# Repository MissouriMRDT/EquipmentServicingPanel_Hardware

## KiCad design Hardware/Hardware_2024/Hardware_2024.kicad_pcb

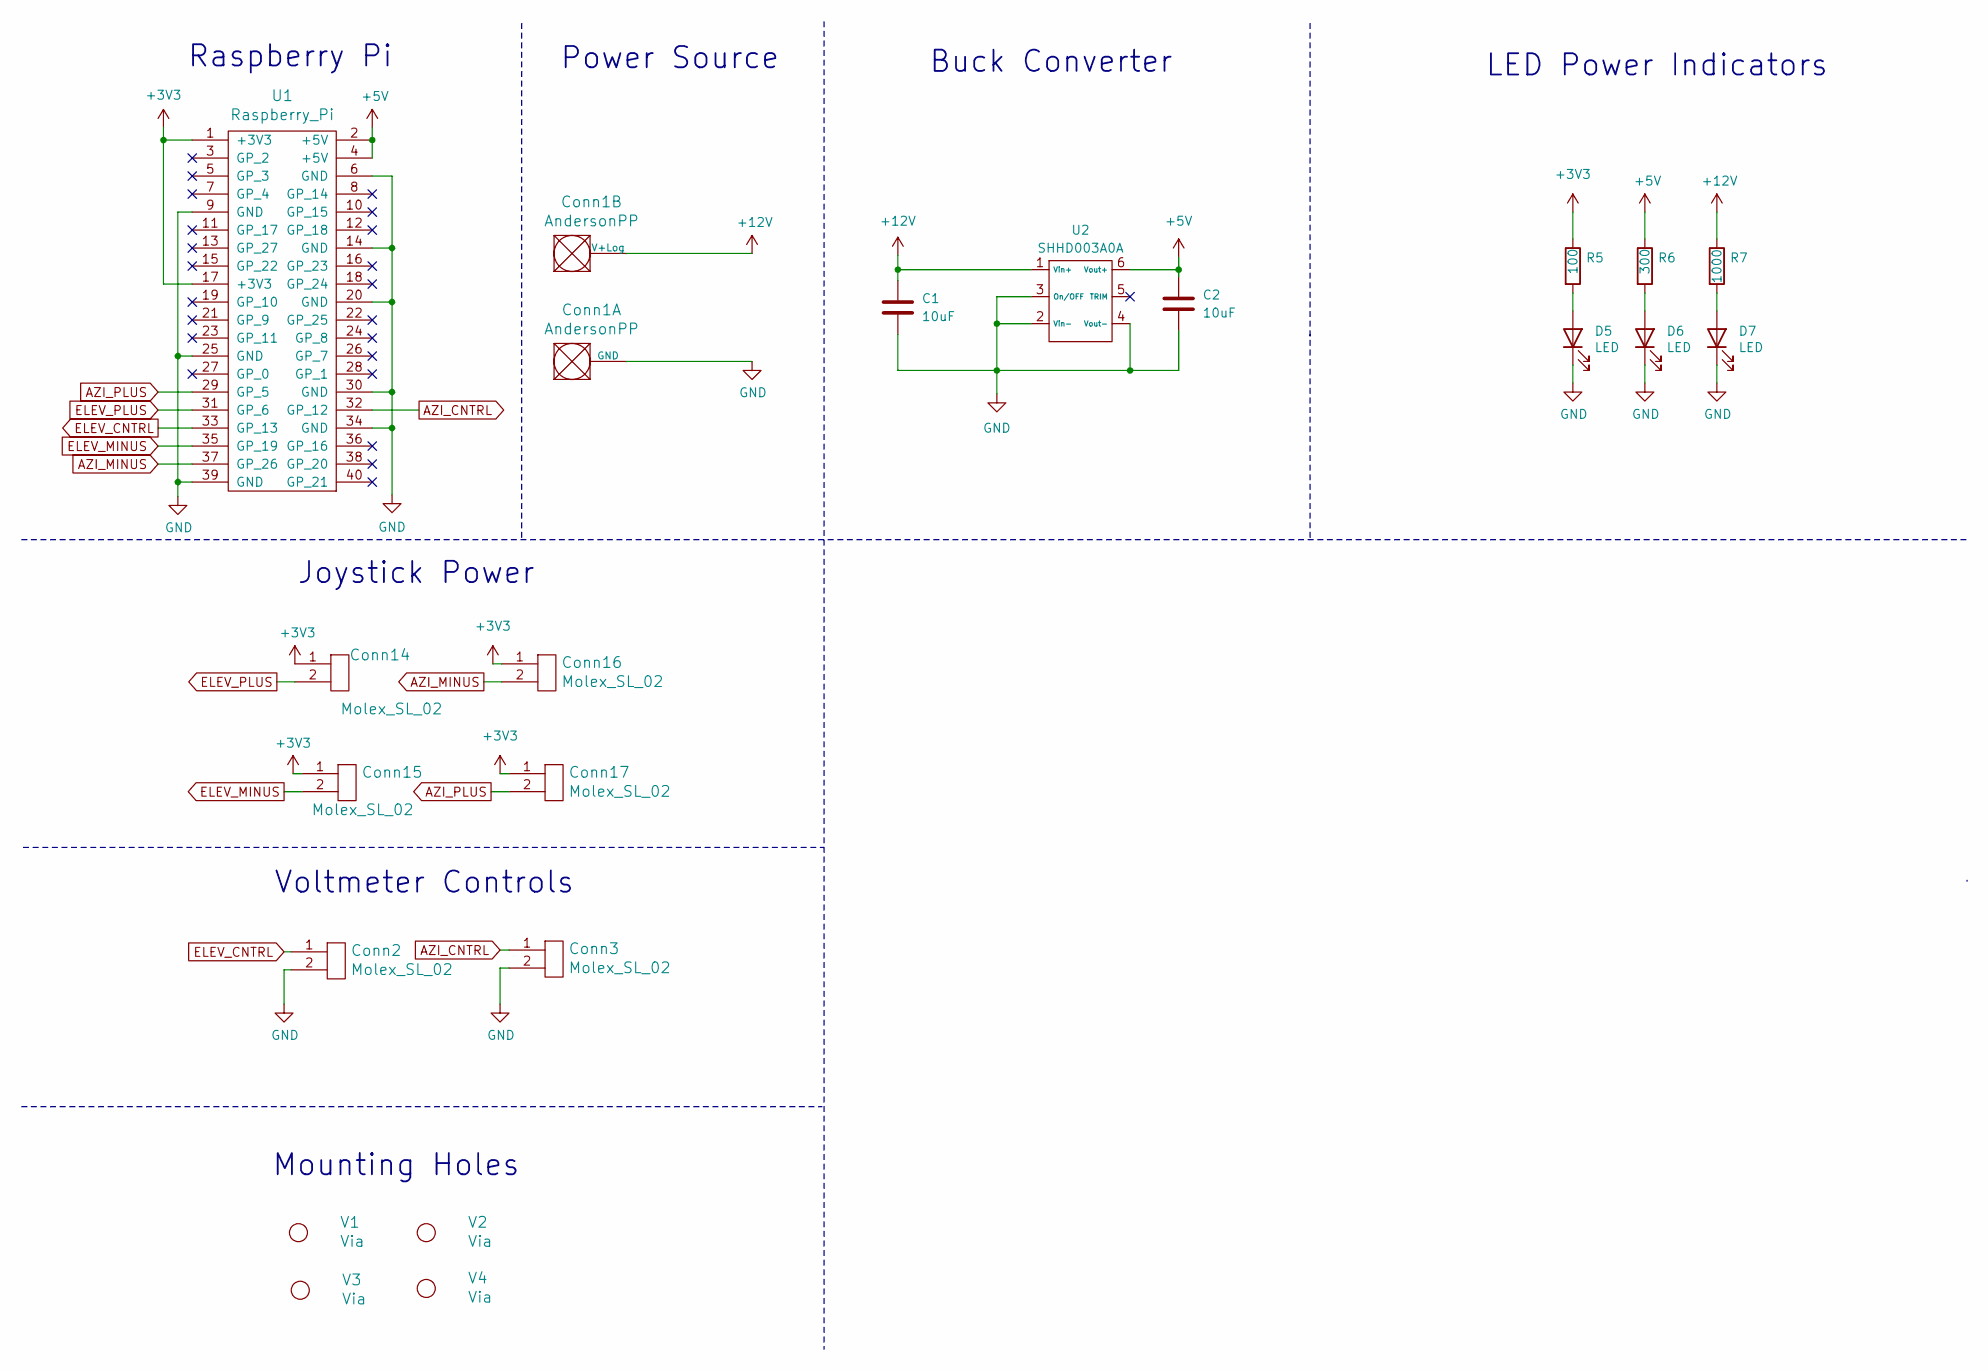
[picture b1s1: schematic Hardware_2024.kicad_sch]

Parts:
C1, C2: 10uF; C_0603_1608Metric
Conn1: AndersonPP; Square_Anderson_2_H_Side_By_Side
Conn2, Conn3, Conn14, Conn15, Conn16, Conn17: Molex_SL_02; MOLEX_SL_02_Vertical
D5, D6, D7: LED; LED_0603_1608Metric_Pad1.05x0.95mm_HandSolder
R5: 100; R_0603_1608Metric_Pad0.98x0.95mm_HandSolder
R6: 300; R_0603_1608Metric_Pad0.98x0.95mm_HandSolder
R7: 1000; R_0603_1608Metric_Pad0.98x0.95mm_HandSolder
U1: Raspberry_Pi; RaspberryPi_THT_BOTTOM
U2: SHHD003A0A; SHHD003A0A41Z_Through_Hole
V1, V2, V3, V4: Via; 4_40_Hole_Corner

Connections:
+3V3: Conn14.1, Conn15.1, Conn16.1, Conn17.1, R5.1, U1.1 (+3V3), U1.17 (+3V3)
+5V: C2.1, R6.1, U1.2 (+5V), U1.4 (+5V), U2.6 (Vout+)
+12V: C1.1, Conn1.2 (V+Log), R7.1, U2.1 (Vin+)
AZI_CNTRL: Conn3.1, U1.32 (GP_12)
AZI_MINUS: Conn16.2, U1.37 (GP_26)
AZI_PLUS: Conn17.2, U1.29 (GP_5)
ELEV_CNTRL: Conn2.1, U1.33 (GP_13)
ELEV_MINUS: Conn15.2, U1.35 (GP_19)
ELEV_PLUS: Conn14.2, U1.31 (GP_6)
GND: C1.2, C2.2, Conn1.1 (GND), Conn2.2, Conn3.2, D5.1 (K), D6.1 (K), D7.1 (K), U1.6 (GND), U1.9 (GND), U1.14 (GND), U1.20 (GND), U1.25 (GND), U1.30 (GND), U1.34 (GND), U1.39 (GND), U2.2 (Vin-), U2.3 (On/OFF), U2.4 (Vout-)
unnamed: D5.2 (A), R5.2
unnamed: D6.2 (A), R6.2
unnamed: D7.2 (A), R7.2

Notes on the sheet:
Raspberry Pi
Power Source
Buck Converter
Joystick Power
Mounting Holes
LED Power Indicators
Voltmeter Controls

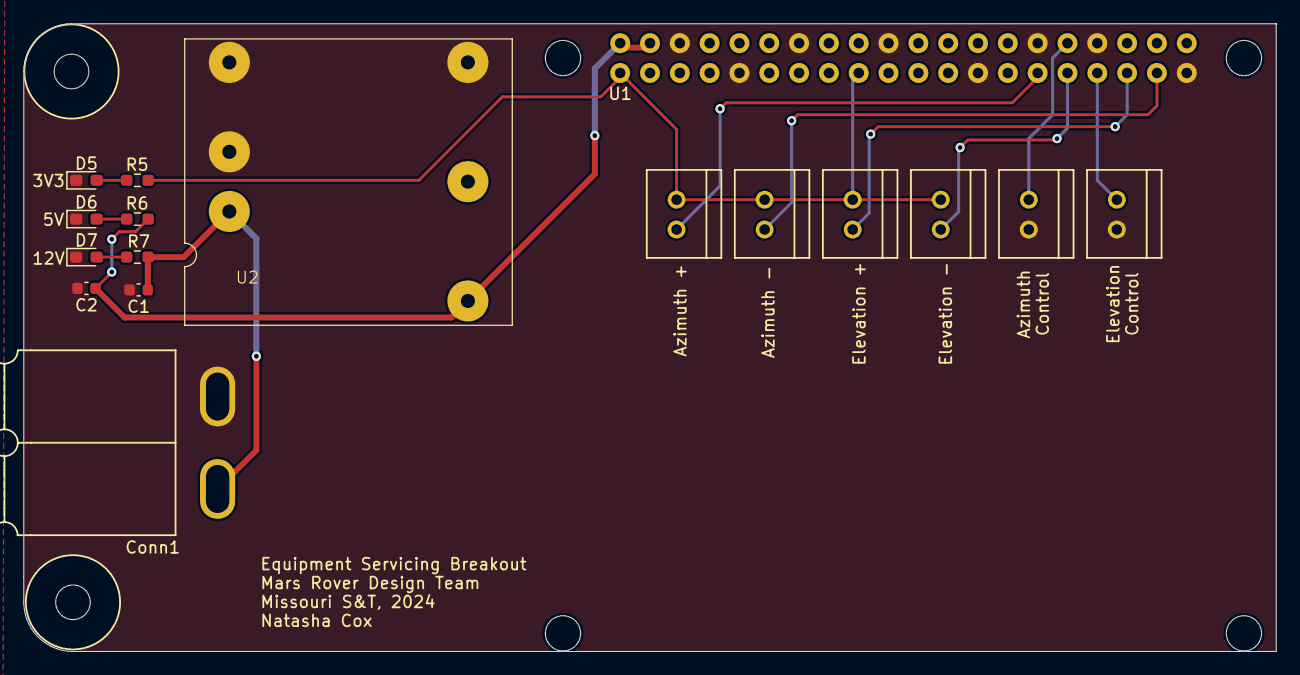
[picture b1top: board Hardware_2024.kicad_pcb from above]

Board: 2 copper layers, 106.7 x 53.5 mm, 21 parts (0 on the bottom side), 13 nets.

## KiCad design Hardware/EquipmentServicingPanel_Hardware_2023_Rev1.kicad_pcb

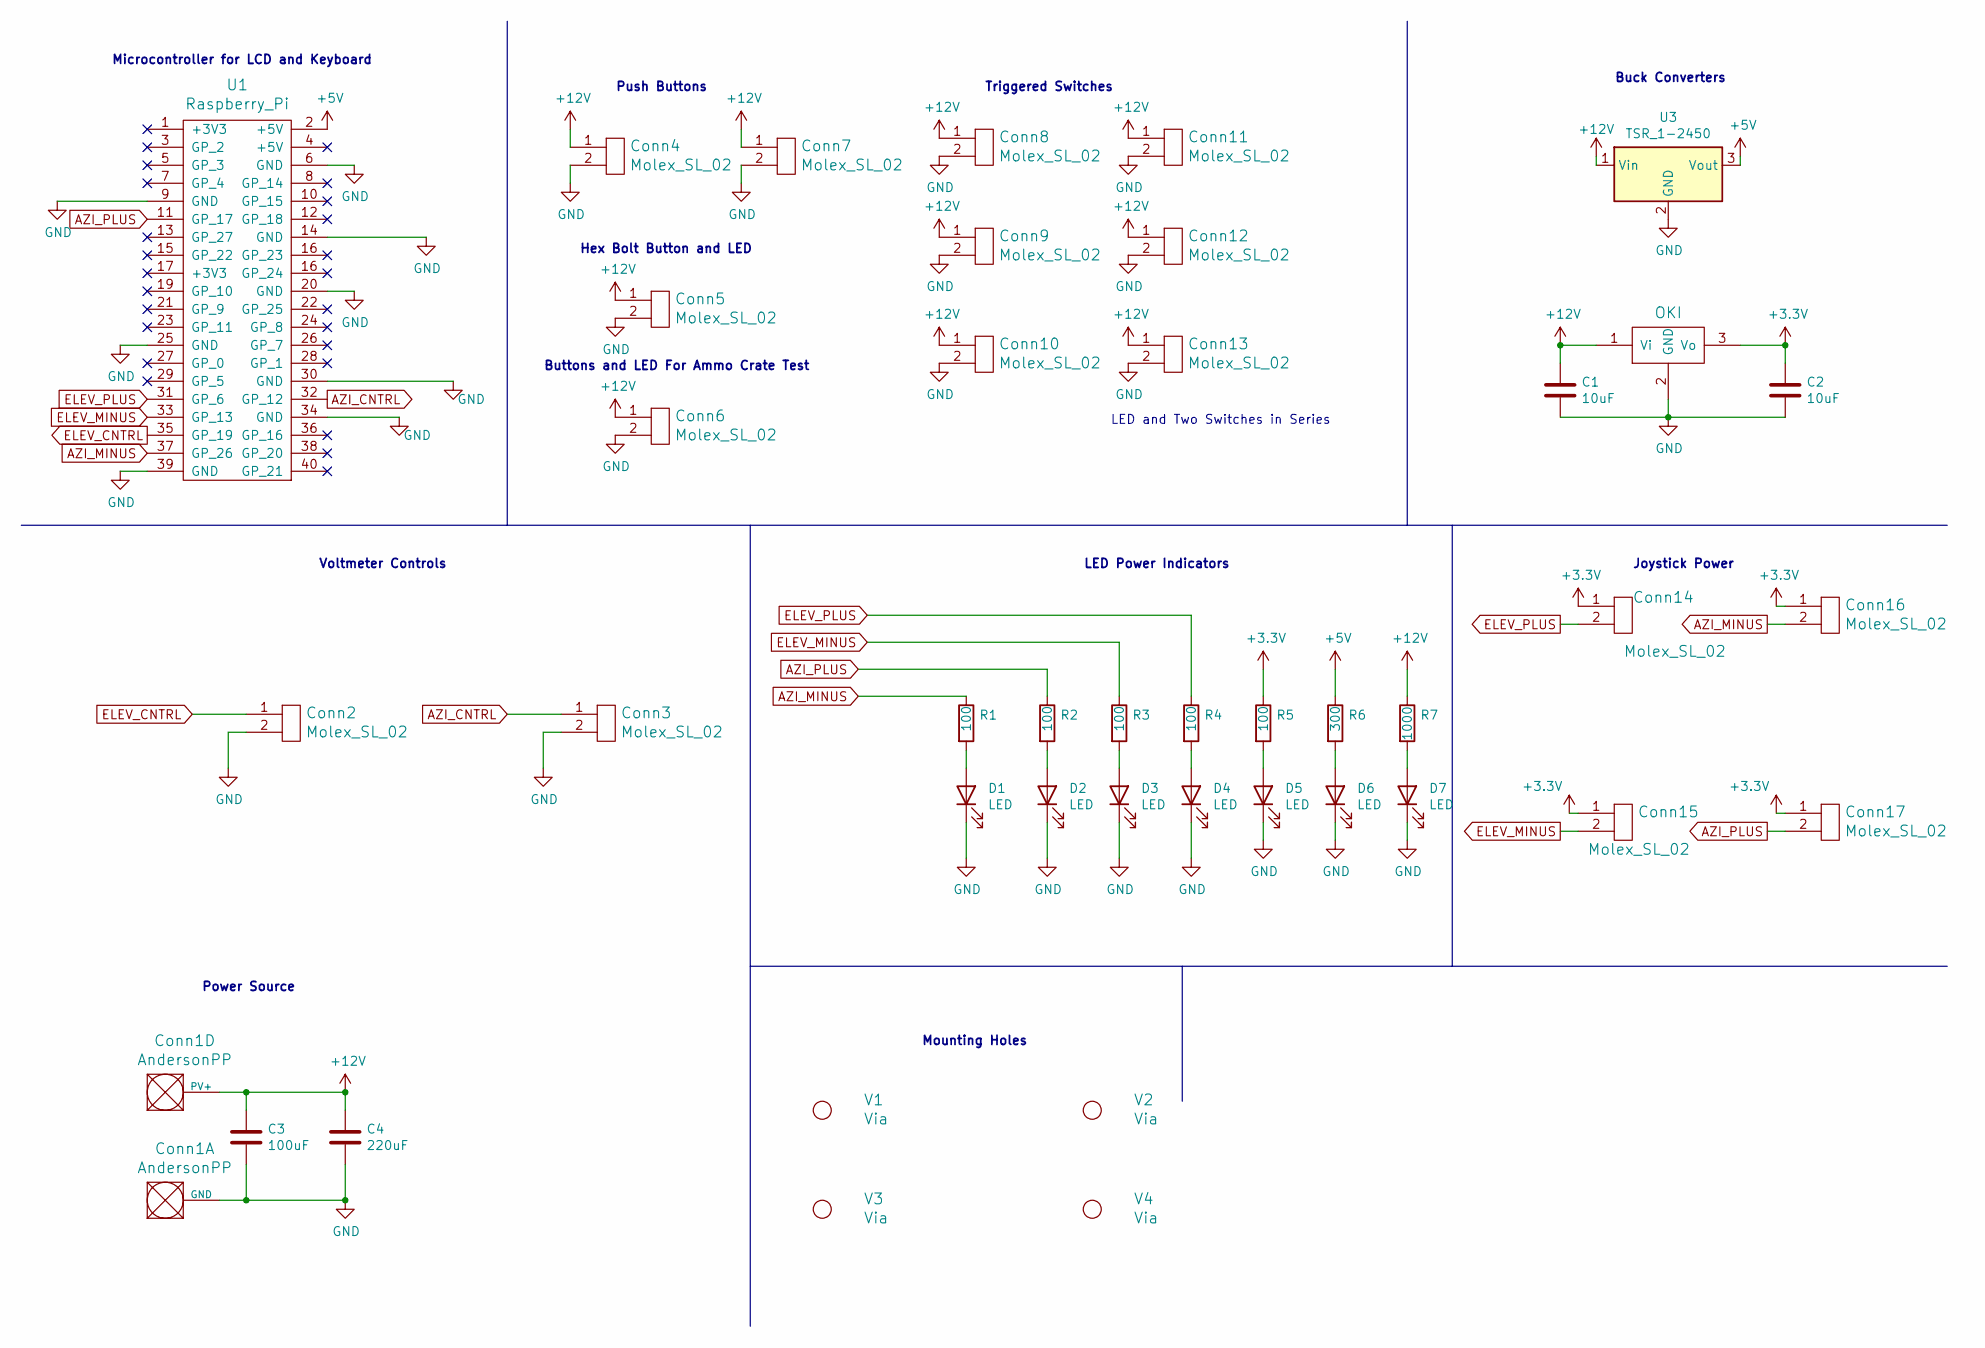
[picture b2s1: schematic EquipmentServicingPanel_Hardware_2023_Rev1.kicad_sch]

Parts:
C1, C2: 10uF; C_0603_1608Metric_Pad1.08x0.95mm_HandSolder
C3: 100uF; CP_Radial_D6.3mm_P2.50mm
C4: 220uF; CP_Radial_D6.3mm_P2.50mm
Conn1: AndersonPP; Square_Anderson_2_H_Stacked
Conn2, Conn3, Conn4, Conn5, Conn6, Conn7, Conn14, Conn16: Molex_SL_02; MOLEX_SL_02_Horizontal
Conn8, Conn9, Conn10, Conn11, Conn12, Conn13, Conn15, Conn17: Molex_SL_02; MOLEX_SL_02_Vertical
D1, D2, D3, D4, D5, D6, D7: LED; LED_0603_1608Metric_Pad1.05x0.95mm_HandSolder
R1, R2, R3, R4, R5: 100; R_0603_1608Metric_Pad0.98x0.95mm_HandSolder
R6: 300; R_0603_1608Metric_Pad0.98x0.95mm_HandSolder
R7: 1000; R_0603_1608Metric_Pad0.98x0.95mm_HandSolder
U1: Raspberry_Pi; RASPBERRY_PI_HEADERS
U2: OKI; OKI_Horizontal
U3: TSR_1-2450; TSR_1-2433
V1, V2, V3, V4: Via; 4_40_Hole_Corner

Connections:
+3V3: C2.1, Conn14.1, Conn15.1, Conn16.1, Conn17.1, R5.1, U2.3 (Vo)
+5V: R6.1, U1.2 (+5V), U3.3 (Vout)
+12V: C1.1, C3.1, C4.1, Conn1.4 (PV+), Conn4.1, Conn5.1, Conn6.1, Conn7.1, Conn8.1, Conn9.1, Conn10.1, Conn11.1, Conn12.1, Conn13.1, R7.1, U2.1 (Vi), U3.1 (Vin)
AZI_CNTRL: Conn3.1, U1.32 (GP_12)
AZI_MINUS: Conn16.2, R1.1, U1.37 (GP_26)
AZI_PLUS: Conn17.2, R2.1, U1.11 (GP_17)
ELEV_CNTRL: Conn2.1, U1.35 (GP_19)
ELEV_MINUS: Conn15.2, R3.1, U1.33 (GP_13)
ELEV_PLUS: Conn14.2, R4.1, U1.31 (GP_6)
GND: C1.2, C2.2, C3.2, C4.2, Conn1.1 (GND), Conn2.2, Conn3.2, Conn4.2, Conn5.2, Conn6.2, Conn7.2, Conn8.2, Conn9.2, Conn10.2, Conn11.2, Conn12.2, Conn13.2, D1.1 (K), D2.1 (K), D3.1 (K), D4.1 (K), D5.1 (K), D6.1 (K), D7.1 (K), U1.6 (GND), U1.9 (GND), U1.14 (GND), U1.20 (GND), U1.25 (GND), U1.30 (GND), U1.34 (GND), U1.39 (GND), U2.2 (GND), U3.2 (GND)
unnamed: D1.2 (A), R1.2
unnamed: D2.2 (A), R2.2
unnamed: D3.2 (A), R3.2
unnamed: D4.2 (A), R4.2
unnamed: D5.2 (A), R5.2
unnamed: D6.2 (A), R6.2
unnamed: D7.2 (A), R7.2

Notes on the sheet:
Buck Converters
Microcontroller for LCD and Keyboard
Buttons and LED For Ammo Crate Test
Push Buttons
Power Source
Hex Bolt Button and LED
Triggered Switches
Joystick Power
Mounting Holes
LED Power Indicators
Voltmeter Controls
LED and Two Switches in Series

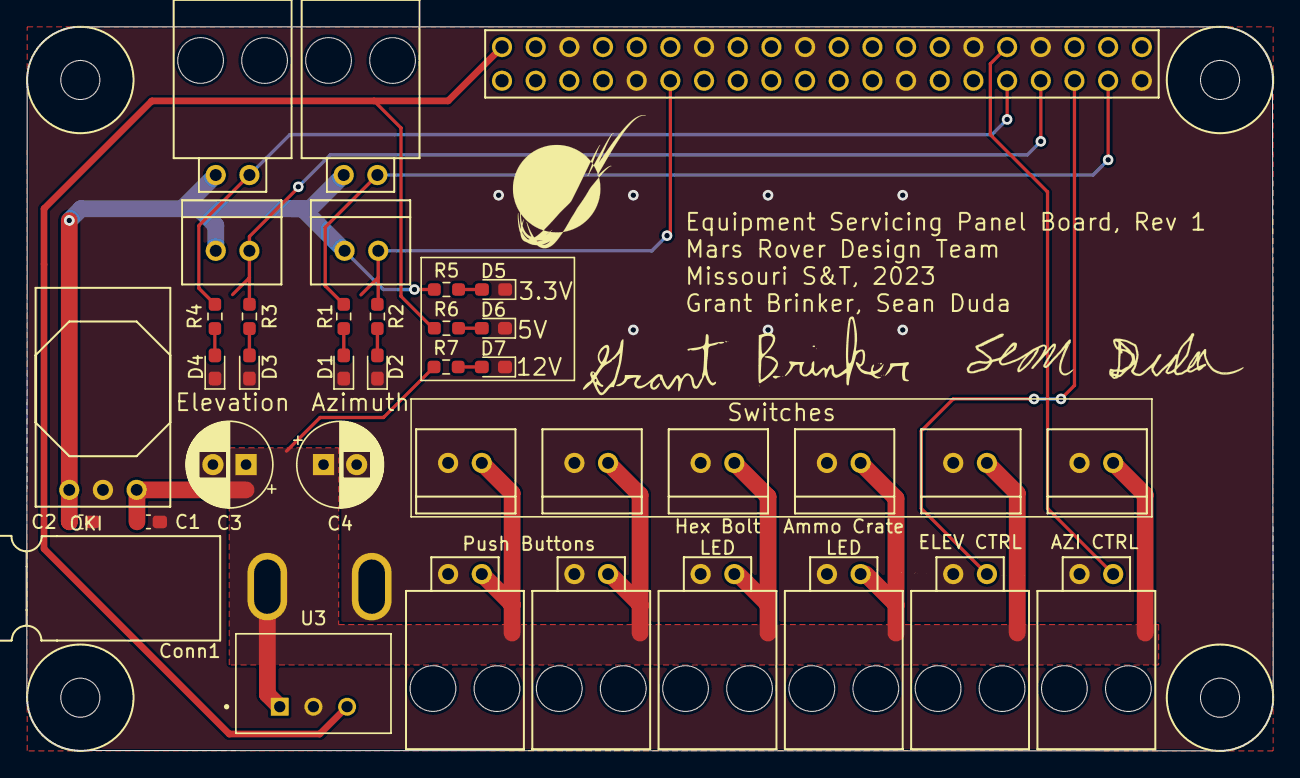
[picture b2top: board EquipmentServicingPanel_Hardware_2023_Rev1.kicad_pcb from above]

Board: 2 copper layers, 94.0 x 54.6 mm, 42 parts (0 on the bottom side), 17 nets.

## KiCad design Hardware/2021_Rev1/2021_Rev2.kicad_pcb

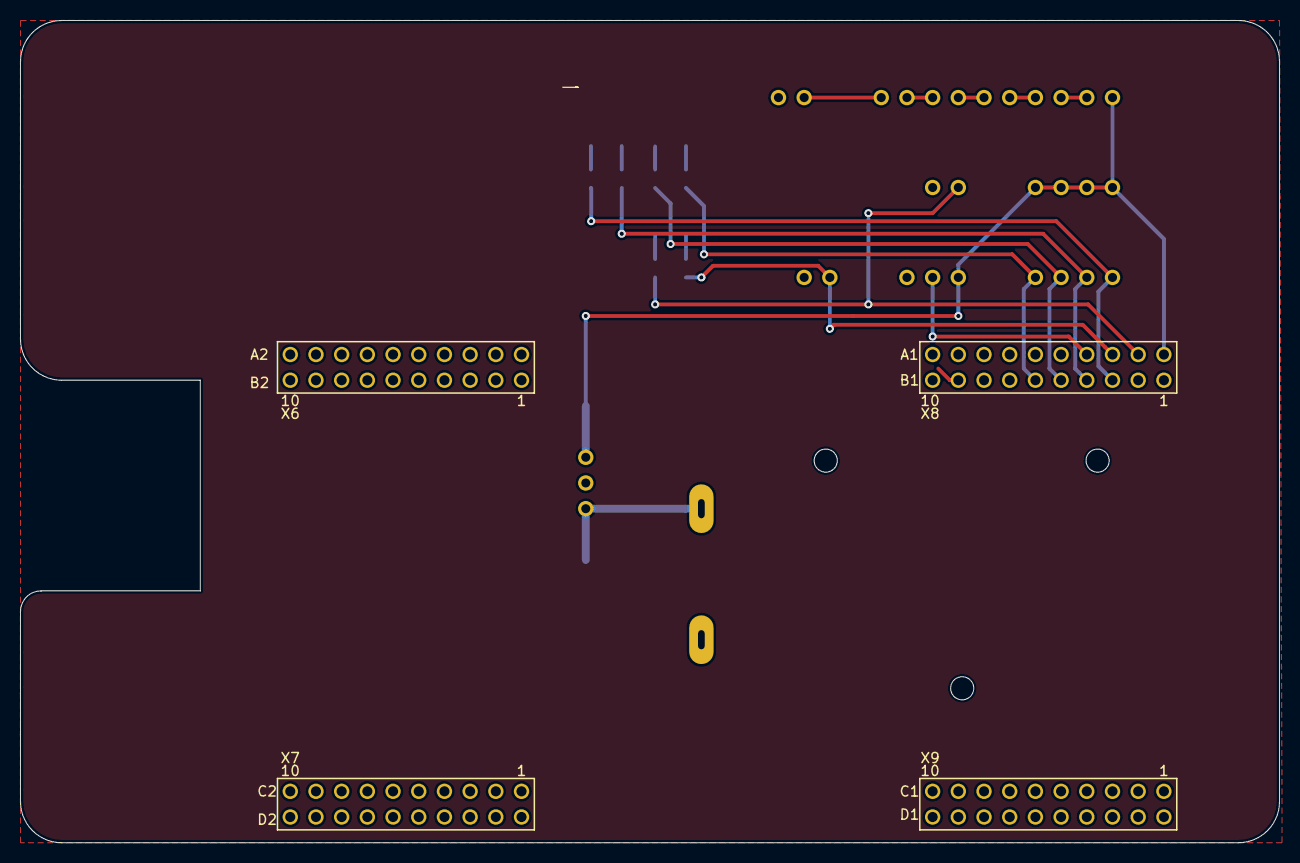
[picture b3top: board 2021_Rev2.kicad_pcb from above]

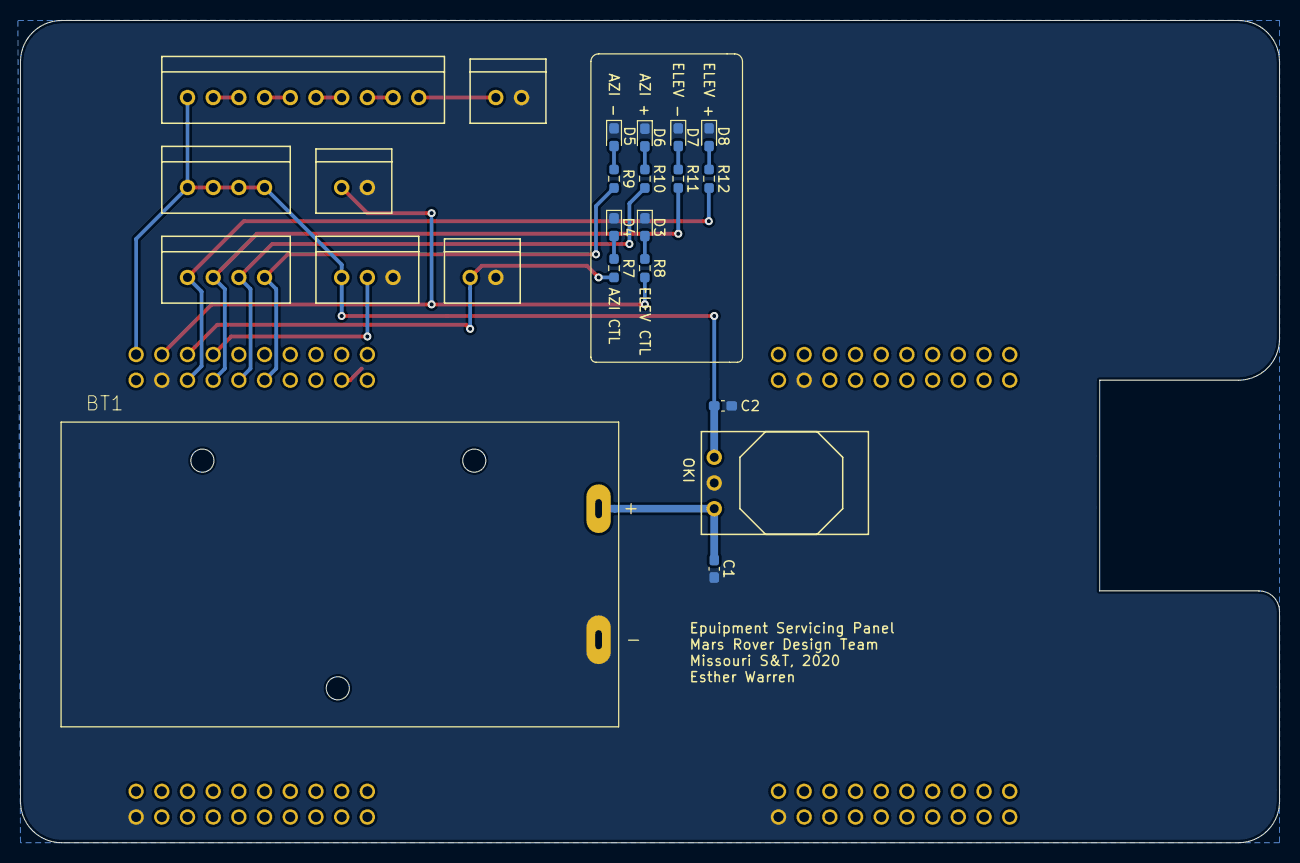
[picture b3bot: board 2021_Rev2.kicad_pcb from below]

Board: 2 copper layers, 124.5 x 81.3 mm, 24 parts (23 on the bottom side), 21 nets.

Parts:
BT1: BC9VPC; BAT_BC9VPC
C1, C2: 10uF; C_0603_1608Metric_Pad1.08x0.95mm_HandSolder
Conn2: Joystick_OUT; MOLEX_SL_04_Vertical
Conn3: Joystick_GND; MOLEX_SL_04_Vertical
Conn4: ELEV; MOLEX_SL_02_Vertical
Conn5: AZI; MOLEX_SL_02_Vertical
Conn6: Switches; MOLEX_SL_10_Vertical
Conn7: Green_LED; MOLEX_SL_02_Vertical
Conn8: Molex_SL_03; MOLEX_SL_03_Vertical
D3, D4, D5, D6, D7, D8: BLUE; LED_0603_1608Metric_Pad1.05x0.95mm_HandSolder
R7, R8, R9, R10, R11, R12: 330; R_0603_1608Metric_Pad0.98x0.95mm_HandSolder
U1: TM4C129E_Launchpad; TM4C129E_Launchpad_FULL_THT_TOP
U2: OKI; OKI_Horizontal

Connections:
+3V3: C2.1, Conn3.1, Conn3.2, Conn3.3, Conn3.4, Conn6.1, Conn8.1, U1.+3V3, U2.3
+9V: BT1.P, C1.1, U2.1
AZI_CTL: Conn5.1, R7.2, U1.PC4
AZI_MINUS: Conn2.4, R9.2, U1.PE3
AZI_PLUS: Conn2.3, R10.2, U1.PE2
ELEV_CTL: Conn4.1, R8.2, U1.PE4
ELEV_MINUS: Conn2.2, R11.2, U1.PE1
ELEV_PLUS: Conn2.1, R12.2, U1.PE0
GND: BT1.N, C1.2, C2.2, Conn4.2, Conn5.2, Conn7.2, Conn8.3, D3.1, D4.1, D5.1, D6.1, D7.1, D8.1, U1.GND, U2.2
LCD_TX: Conn8.2, U1.PC5
unnamed: Conn6.2, Conn6.3
unnamed: Conn6.4, Conn6.5
unnamed: Conn6.6, Conn6.7
unnamed: Conn6.8, Conn6.9
unnamed: Conn6.10, Conn7.1
unnamed: D3.2, R8.1
unnamed: D4.2, R7.1
unnamed: D5.2, R9.1
unnamed: D6.2, R10.1
unnamed: D7.2, R11.1
unnamed: D8.2, R12.1

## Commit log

2020-10-28 Schematic started
    TIVA,BUCK,USB added
2020-11-05 Schematic almost finished
    Switches, Joystick connector, Analog gauge
2020-11-05 Schematic almost finished
    added LCD display
2020-11-18 Layout Started
    Bucks and LCD circuit replaced with OKIs and spark fun LCD
2020-11-25 resistor values added to CTL pins
2020-11-25 Updated Schematic and Layout
    Changed joystick pins from GND to 3.3V and updated USB circuit to a known working circuit
2020-11-29 Finished Layout and Post CDR Checklist
2020-11-29 Finished Layout
2020-12-01 Added Signature
2020-12-01 tiva footprint changed to THT_BOTTOM
2020-12-01 Revert "tiva footprint changed to THT_BOTTOM"
    This reverts commit b87381c65a80fcd5fad75ae35fe4b21bdfbb7d2f.
2020-12-01 nvm we did a jank fix
    changing the footprint broke everything so we just flipped the board and then flipped the tiva to the front.
2020-12-01 Layout Finished
2021-02-22 Attempt to fix FT230X
2021-02-22 Attempted fix of USB circuit
2021-04-25 Rev2 Update
    Swapped the ctl pins to usable ones and removed usb/keyboard functionality and 5v regular for usb
2023-03-11 Added 2023 Rev 1
    Added 2023 Rev 1 ESP files
2023-03-11 Revert "Added 2023 Rev 1"
    This reverts commit 6598b15f7e0e5b1d5f2691bb70ff06166af6fbd9.
2023-03-11 Added 2023 Rev 1 files
    Added 2023 Rev 1 files
2023-03-20 fixed git issues
2023-03-20 Added Vias and removed extra voltmeter
    Added vias and removed one of the three voltmeters that used a potentiometer to test the wrist
2023-03-20 changes were made to fix pin 16 issues
    different ports were used on the raspberry pi so no connects could be placed on the duplicated pin 16
2023-03-20 Applied Kicad footprints
    Applied Equipment Servicing footprints
2023-03-20 Revert "Applied Kicad footprints"
    This reverts commit d56fd15f2c9d233914814fde713dd6368af3c8bd.
2023-03-20 Created Layout
    Created Layout for PCB design of Equipment Servicing Panel
2023-03-20 Made layout
2023-03-21 generated gerbs
2024-03-06 schematic work
    Almost finished, still needs work on potentiometer
2024-03-06 added potentiometer circuit
2024-03-07 assigned footprints worked on layout
2024-03-07 finished organizing. traces need work
2024-03-08 worked on traces a bit
2024-03-09 Finished traces
2024-03-12 Added some vias
2024-03-21 Updated with changes
2024-03-26 created gerbs
2024-03-26 Generated BOM
